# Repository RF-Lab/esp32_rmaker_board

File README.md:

# esp32_rmaker_board

Rmaker is open source [Rain Maker](https://rainmaker.espressif.com/) ready home automation controller. This board includes:

* [ESP32 DevKit](https://www.aliexpress.com/wholesale?catId=0&initiative_id=SB_20210715114037&SearchText=esp32).
* 6 buffered open collector interfaces for switch control.
* 3 pull-up input interfaces for push buttons or dry electrode or other 1-pin digital sensors (like Hall-sensor).
* Onboard DHT-22 thermometer.
* 1 pre-conditioned ADC input for water pressure or similar sensor.
* Firmware examples based on Espressif code can be found [Here](https://github.com/RF-Lab/esp32_rmaker_sw)

# esp32_rmaker_board installed to Legrand LX3

# esp32_rmaker_board installed to Legrand Plexo

# Schematic

# PCB

# [Rain Maker](https://rainmaker.espressif.com/) Android app interface example

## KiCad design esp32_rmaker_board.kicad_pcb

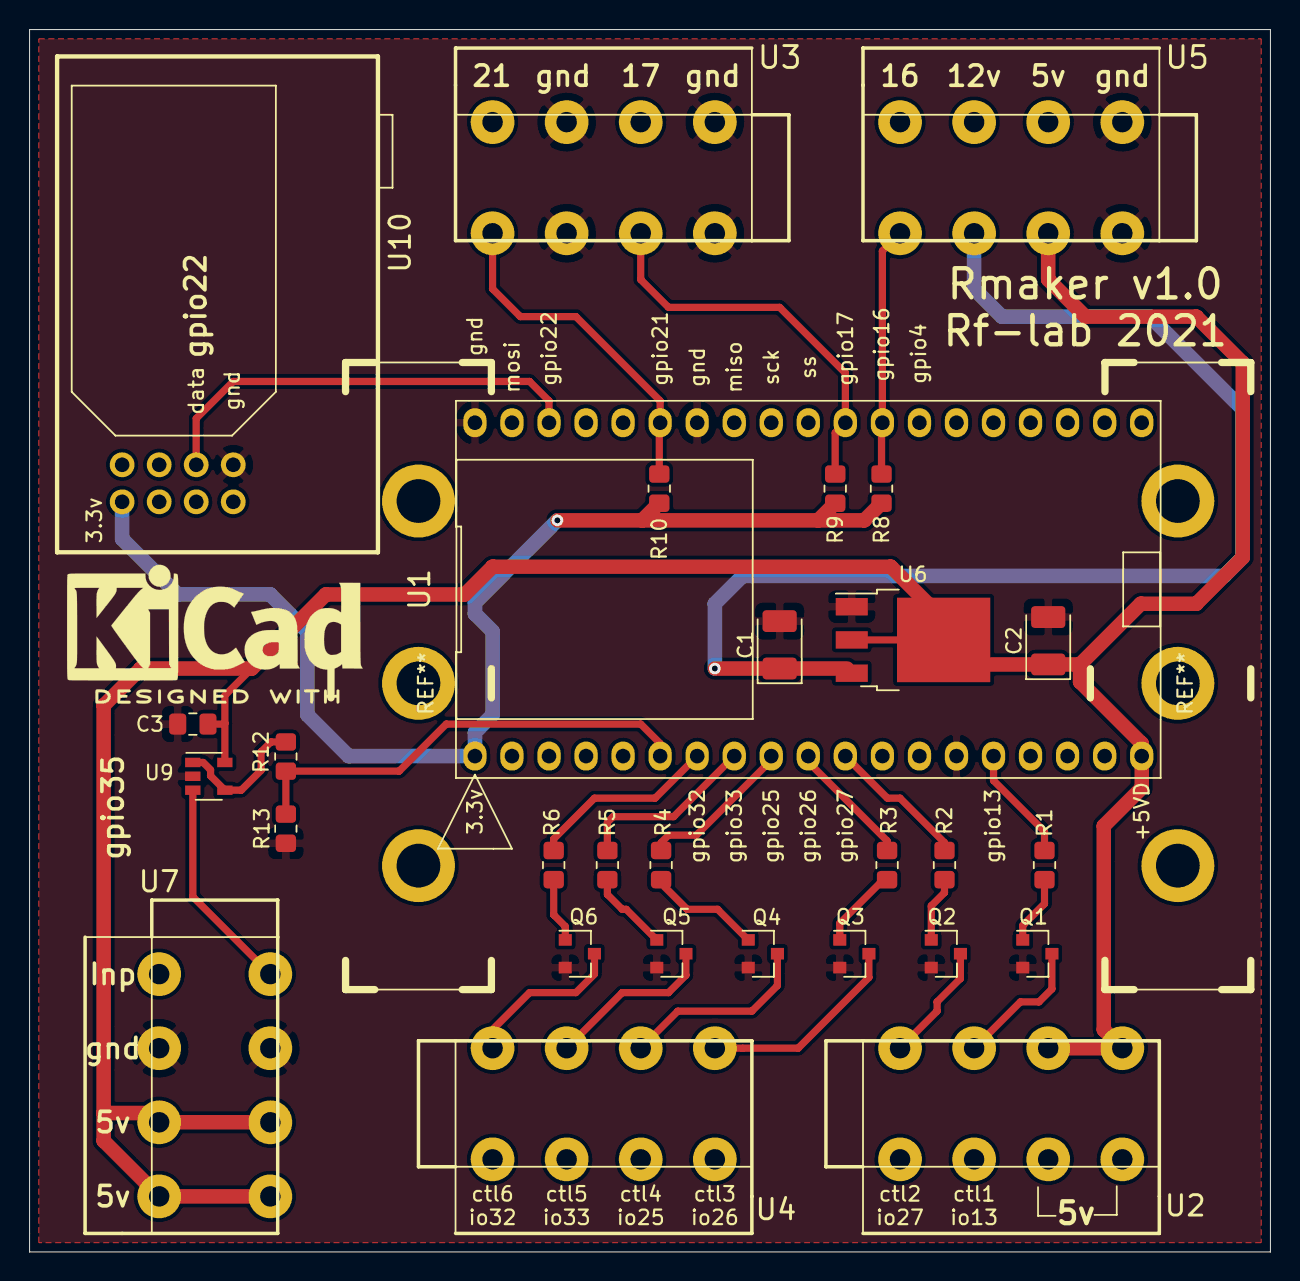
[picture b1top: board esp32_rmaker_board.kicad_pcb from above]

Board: 2 copper layers, 85.1 x 83.8 mm, 29 parts (0 on the bottom side), 29 nets.

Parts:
C1, C2: CP1; CP_EIA-3528-21_Kemet-B_Pad1.50x2.35mm_HandSolder
C3: 0.1; C_0805_2012Metric_Pad1.18x1.45mm_HandSolder
Q1, Q2, Q3, Q4, Q5, Q6: BC817; SOT-23
R1, R2, R3, R4, R5, R6, R13: 1k; R_0805_2012Metric_Pad1.20x1.40mm_HandSolder
R8, R9, R10: 10k; R_0805_2012Metric_Pad1.20x1.40mm_HandSolder
R12: 4k; R_0805_2012Metric_Pad1.20x1.40mm_HandSolder
U1: ESP32-DevKitC-MCU_Espressif; DIP-38_W22.86m_P2.54mm_ESP32_DevKitC
U2, U3, U4, U5, U7: DG142V-5.08-4
U6: LM1117-5.0; TO-252-3_TabPin2
U9: OPA340NA; SOT-23-5
U10: DHT22

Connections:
3v3: R8.2, R9.2, R10.2, U1.1, U10.1
5v: C2.1, C3.1, U1.19, U2.5, U2.6, U5.7, U6.2, U7.3, U7.4, U7.5, U7.6, U9.5
GND: C1.2, C2.2, C3.2, Q1.2, Q2.2, Q3.2, Q4.2, Q5.2, Q6.2, R13.1, U1.14, U1.32, U1.38, U3.1, U3.3, U3.6, U3.8, U5.1, U5.8, U6.1, U7.2, U7.7, U9.2, U10.5
unnamed: Q1.1, R1.1
unnamed: Q2.1, R2.1
unnamed: Q3.1, R3.1
unnamed: Q4.1, R4.1
unnamed: Q5.1, R5.1
unnamed: Q6.1, R6.1
unnamed: R12.2, U9.1, U9.4
adcInp: U7.8, U9.3
ext_6.5_12v: C1.1, U5.6, U6.3
gpio13: R1.2, U1.15
gpio16: R8.1, U1.27, U5.5
gpio17: R9.1, U1.28, U3.7
gpio21: R10.1, U1.33, U3.5
gpio22: U1.36, U10.6
gpio25: R4.2, U1.9
gpio26: R3.2, U1.10
gpio27: R2.2, U1.11
gpio32: R6.2, U1.7
gpio33: R5.2, U1.8
gpio35: R12.1, R13.2, U1.6
outCtl1: Q1.3, U2.7
outCtl2: Q2.3, U2.8
outCtl3: Q3.3, U4.5
outCtl4: Q4.3, U4.6
outCtl5: Q5.3, U4.7
outCtl6: Q6.3, U4.8

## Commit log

2021-07-14 v1.0
